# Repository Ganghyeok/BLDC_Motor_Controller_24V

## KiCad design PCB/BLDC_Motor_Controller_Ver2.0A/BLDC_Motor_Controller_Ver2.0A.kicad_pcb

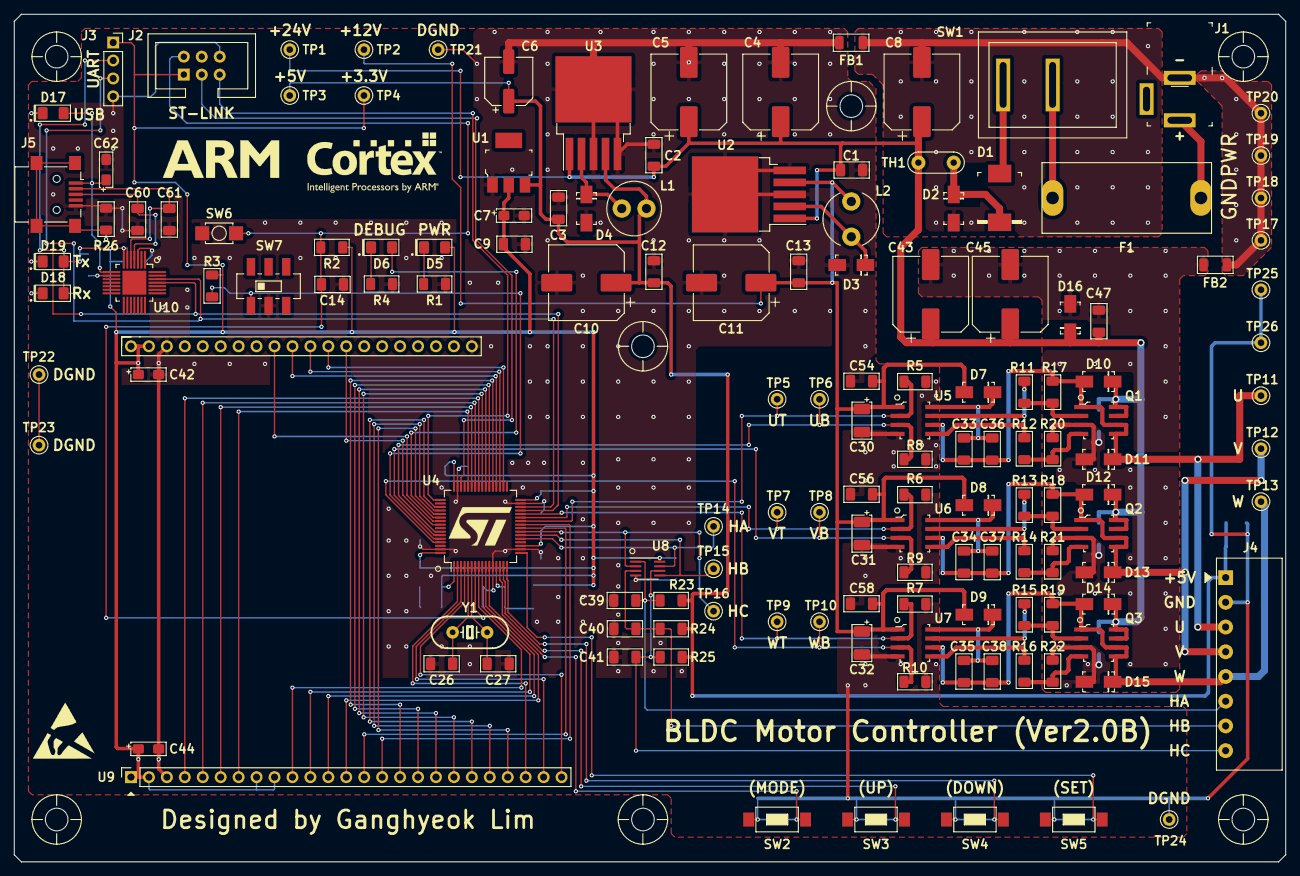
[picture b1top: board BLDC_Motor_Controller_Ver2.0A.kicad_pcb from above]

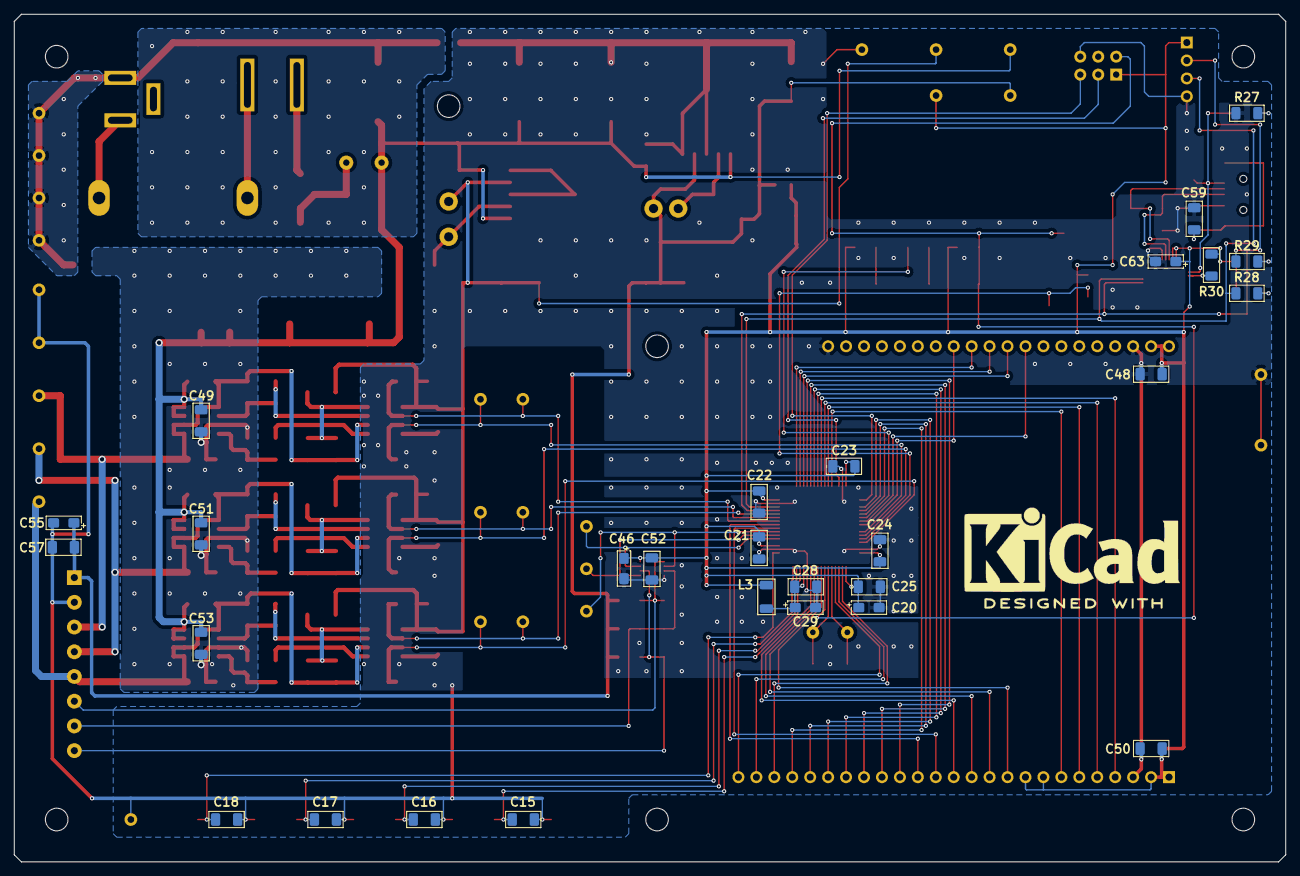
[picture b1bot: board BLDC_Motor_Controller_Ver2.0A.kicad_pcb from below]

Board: 2 copper layers, 180.0 x 120.0 mm, 170 parts (28 on the bottom side), 92 nets.

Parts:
C1, C2, C3, C9, C12, C13, C14, C21, C22, C23, C24, C25, C28, C36, C37, C38, C47, C48, C49, C50, C51, C52, C53, C54, C56, C57, C58, C59: 100nF; C3216_Metric
C4, C5, C8, C10, C11: 330uF/35V; CP_Elec_10x10.5
C6: 100uF/16V; CP_Elec_6.3x5.3
C7, C20, C42, C44, C46, C55: 10uF/16V; C3216_Tantal_Metric
C15, C16, C17, C18: 220nF(ED); C3216_Metric
C26, C27: 20pF; C3216_Metric
C29, C62, C63: 1uF/16V; C3216_Tantal_Metric
C30, C31, C32: 10uF/25V; C3528_Tantal_Metric
C33, C34, C35: 2.2uF; C3216_Metric
C39, C40, C41: 330pF; C3216_Metric
C43, C45: 470uF/35V; CP_Elec_10x10.5
C60, C61: 15pF; C3216_Metric
D1: SS34; DO-214AB
D2, D16: SMAJ24A; DO-214AC
D3, D4: SS13; DO-214AC
D5: LED(POWER); LED_3216_Metric
D6: LED(DEBUG); LED_3216_Metric
D7, D8, D9: SS14; DO-214AC
D10, D11, D12, D13, D14, D15: RS1G; DO-214AC
D17, D18, D19: LED; LED_3216_Metric
F1: 250V/1A; GF-205B(20mm)
FB1, FB2: ED; L3216_Metric
J1: POWER_CONNECTOR; Barrel_Jack_5.5mmODx2.1mmID_PJ-202A
J2: ST-Link_Connector; BHS-01-6P
J3: UART_Connector; PinSocket_1x04_P2.54mm_Vertical
J4: Conn_01x08; Terminal_Block_3.5mm_8P
J5: USB_B_Mini; USB_Mini-B_Lumberg_2486_01_Horizontal
L1: 470uH; L_Radial_D7.5mm_P3.50mm_Fastron_07P
L2: 1mH; L_Radial_D7.8mm_P5.00mm_Fastron_07HCP
L3: 10uH; L3216_Metric
Q1, Q2, Q3: IRF7351PBF; SOIC-8_W3.9mm
R1, R4, R28, R29: 220; R3216_Metric
R2: 100k; R3216_Metric
R3, R5, R6, R7, R8, R9, R10, R17, R18, R19, R20, R21, R22: 10k; R3216_Metric
R11, R12, R13, R14, R15, R16: 22; R3216_Metric
R23, R24, R25, R30: 4.7k; R3216_Metric
R26: 1M; R3216_Metric
R27: 330; R3216_Metric
SW1: SW(POWER); KCD1-101A
SW2: SW(MODE); ITS-1107(SMD)
SW3: SW(UP); ITS-1107(SMD)
SW4: SW(DOWN); ITS-1107(SMD)
SW5: SW(START/STOP); ITS-1107(SMD)
SW6: SW(RESET); SW_TACT_SMD_W3.9mm_L2.9mm_H2mm_GH
SW7: SW(BOOT0); SW_Slide_6P_SMD_GH
TH1: 5D9; NTC-5D-7_9
TP1: TP(+24V); Test_Point(Loop)
TP2: TP(+12V); Test_Point(Loop)
TP3: TP(+5V); Test_Point(Loop)
TP4: TP(+3.3V); Test_Point(Loop)
TP5: UT; Test_Point(Loop)
TP6: UB; Test_Point(Loop)
TP7: VT; Test_Point(Loop)
TP8: VB; Test_Point(Loop)
TP9: WT; Test_Point(Loop)
TP10: WB; Test_Point(Loop)
TP11: U; Test_Point(Loop)
TP12: V; Test_Point(Loop)
TP13: W; Test_Point(Loop)
TP14: HA; Test_Point(Loop)
TP15: HB; Test_Point(Loop)
TP16: HC; Test_Point(Loop)
TP17, TP18, TP19, TP20: AGND; Test_Point(Loop)
TP21, TP22, TP23, TP24, TP25, TP26: DGND; Test_Point(Loop)
U1: LM1117-3.3; SOT-223
U2: LM2575-12BU; TO-263-5_TabPin3
U3: LM2575-5.0BU; TO-263-5_TabPin3
U4: STM32F103RCTx; LQFP-64_10x10mm_P0.5mm
U5, U6, U7: IR2101; SOIC-8_W3.9mm
U8: SN74LVC3G17; SSOP-8_2.95x2.8mm_P0.65mm
U9: TFT-32A
U10: CP2102; VFQFN-28-1EP_5x5mm_HandSolder
Y1: 8MHz; CRYSTAL_HC49_PTH

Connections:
+3.3V: C7.1, C9.1, C20.1, C21.1, C22.1, C23.1, C24.1, C25.1, C42.1, C44.1, C46.1, C48.1, C50.1, C52.1, C63.1, D5.2, D18.2, D19.2, J2.1, J3.1, L3.2, R2.1, R3.1, R30.1, TP4.1, U1.2, U4.1, U4.19, U4.32, U4.48, U4.64, U8.8, U9.1, U9.2, U9.8, U9.9, U9.26, U9.27, U10.6, U10.7
+5V: C3.1, C6.1, C10.1, C12.1, C55.1, C57.1, J4.1, L1.2, R23.1, R24.1, R25.1, TP3.1, U1.3, U3.4
+12V: C11.1, C13.1, C30.1, C31.1, C32.1, C54.1, C56.1, C58.1, D7.A, D8.A, D9.A, L2.2, TP2.1, U2.4, U5.1, U6.1, U7.1
+24V: C1.1, C2.1, C4.1, C5.1, C8.1, C43.1, C45.1, C47.1, C49.1, C51.1, C53.1, D10.K, D12.K, D14.K, D16.K, Q1.7, Q1.8, Q2.7, Q2.8, Q3.7, Q3.8, TH1.1, TP1.1, U2.1, U3.1
BOOT0: R3.2, SW7.1, U4.60
D+: C60.1, J5.3, U10.4
D-: C61.1, J5.2, U10.5
DEBUG1: D6.2, U4.54
GND: C1.2, C2.2, C3.2, C4.2, C5.2, C6.2, C7.2, C9.2, C10.2, C11.2, C12.2, C13.2, C14.2, C15.2, C16.2, C17.2, C18.2, C20.2, C21.2, C22.2, C23.2, C24.2, C25.2, C26.2, C27.2, C28.2, C29.2, C30.2, C31.2, C32.2, C39.2, C40.2, C41.2, C42.2, C44.2, C46.2, C48.2, C50.2, C52.2, C54.2, C55.2, C56.2, C57.2, C58.2, C59.2, C60.2, C61.2, C62.2, C63.2, D3.A, D4.A, FB1.2, J2.6, J3.4, J4.2, J5.5, R1.2, R4.2, R5.2, R6.2, R7.2, R8.2, R9.2, R10.2, R26.1, R27.1, SW2.1, SW3.1, SW4.1, SW5.1, SW6.2, SW7.2, TP21.1, TP22.1, TP23.1, TP24.1, TP25.1, TP26.1, U1.1, U2.3, U2.5, U3.3, U3.5, U4.12, U4.18, U4.31, U4.47, U4.63, U5.4, U6.4, U7.4, U8.4, U9.3, U9.28, U9.45, U10.3
GNDA: C43.2, C45.2, C47.2, C49.2, C51.2, C53.2, D11.A, D13.A, D15.A, D16.A, FB2.1, Q1.3, Q2.3, Q3.3, R20.1, R21.1, R22.1
GNDPWR: C8.2, D2.A, FB1.1, FB2.2, J1.2, TP17.1, TP18.1, TP19.1, TP20.1
HA: TP14.1, U4.21, U8.7
HB: TP15.1, U4.22, U8.5
HC: TP16.1, U4.23, U8.2
NRST: C14.1, J2.2, R2.2, SW6.1, U4.7
unnamed: C26.1, U4.5, Y1.1
unnamed: C27.1, U4.6, Y1.2
unnamed: C28.1, C29.1, L3.1, U4.13
unnamed: C33.1, C36.1, D7.K, U5.8
unnamed: C33.2, C36.2, D10.A, D11.K, J4.3, Q1.1, Q1.5, Q1.6, R17.1, TP11.1, U5.6
unnamed: C34.1, C37.1, D8.K, U6.8
unnamed: C34.2, C37.2, D12.A, D13.K, J4.4, Q2.1, Q2.5, Q2.6, R18.1, TP12.1, U6.6
unnamed: C35.1, C38.1, D9.K, U7.8
unnamed: C35.2, C38.2, D14.A, D15.K, J4.5, Q3.1, Q3.5, Q3.6, R19.1, TP13.1, U7.6
unnamed: C39.1, J4.6, R23.2, U8.1
unnamed: C40.1, J4.7, R24.2, U8.3
unnamed: C41.1, J4.8, R25.2, U8.6
unnamed: C59.1, J5.6, R26.2
unnamed: D1.A, SW1.2
unnamed: D1.K, D2.K, TH1.2
unnamed: D3.K, L2.1, U2.2
unnamed: D4.K, L1.1, U3.2
unnamed: D5.1, R1.1
unnamed: D6.1, R4.1
unnamed: D17.1, R27.2
unnamed: D18.1, R28.2
unnamed: D19.1, R29.2
unnamed: F1.1, SW1.1
unnamed: F1.2, J1.1
unnamed: Q1.2, R11.1, R17.2
unnamed: Q1.4, R12.1, R20.2
unnamed: Q2.2, R13.1, R18.2
unnamed: Q2.4, R14.1, R21.2
unnamed: Q3.2, R15.1, R19.2
unnamed: Q3.4, R16.1, R22.2
unnamed: R11.2, U5.7
unnamed: R12.2, U5.5
unnamed: R13.2, U6.7
unnamed: R14.2, U6.5
unnamed: R15.2, U7.7
unnamed: R16.2, U7.5
unnamed: R30.2, U10.9
SPI2_MISO: U4.35, U9.36
SPI2_MOSI: U4.36, U9.35
SPI2_SCK: U4.34, U9.37
SW1: C15.1, SW2.2, U4.14
SW2: C16.1, SW3.2, U4.15
SW3: C17.1, SW4.2, U4.16
SW4: C18.1, SW5.2, U4.17
SWCLK: J2.5, U4.49
SWDIO: J2.3, U4.46
TFT_D0: U4.8, U9.10
TFT_D1: U4.9, U9.11
TFT_D2: U4.10, U9.12
TFT_D3: U4.11, U9.13
TFT_D4: U4.24, U9.14
TFT_D5: U4.25, U9.15
TFT_D6: U4.37, U9.16
TFT_D7: U4.38, U9.17
TFT_D8: U4.39, U9.18
TFT_D9: U4.40, U9.19
TFT_D10: U4.51, U9.20
TFT_D11: U4.52, U9.21
TFT_D12: U4.53, U9.22
TFT_D13: U4.2, U9.23
TFT_D14: U4.3, U9.24
TFT_D15: U4.4, U9.25
TFT_RS: U4.43, U9.6
UART3_RX: J3.3, R28.1, U4.30, U10.26
UART3_TX: J3.2, R29.1, U4.29, U10.25
UB: R8.1, TP6.1, U4.58, U5.3
UT: R5.1, TP5.1, U4.26, U5.2
VB: R9.1, TP8.1, U4.59, U6.3
VBUS: C62.1, D17.2, J5.1, U10.8
VT: R6.1, TP7.1, U4.27, U6.2
WB: R10.1, TP10.1, U4.61, U7.3
WT: R7.1, TP9.1, U4.28, U7.2
~TFT_CS: U4.42, U9.5
~TFT_RST: U4.41, U9.4
~TFT_WR: U4.44, U9.7
~TS_CS: U4.55, U9.34
~TS_INT: U4.56, U9.38

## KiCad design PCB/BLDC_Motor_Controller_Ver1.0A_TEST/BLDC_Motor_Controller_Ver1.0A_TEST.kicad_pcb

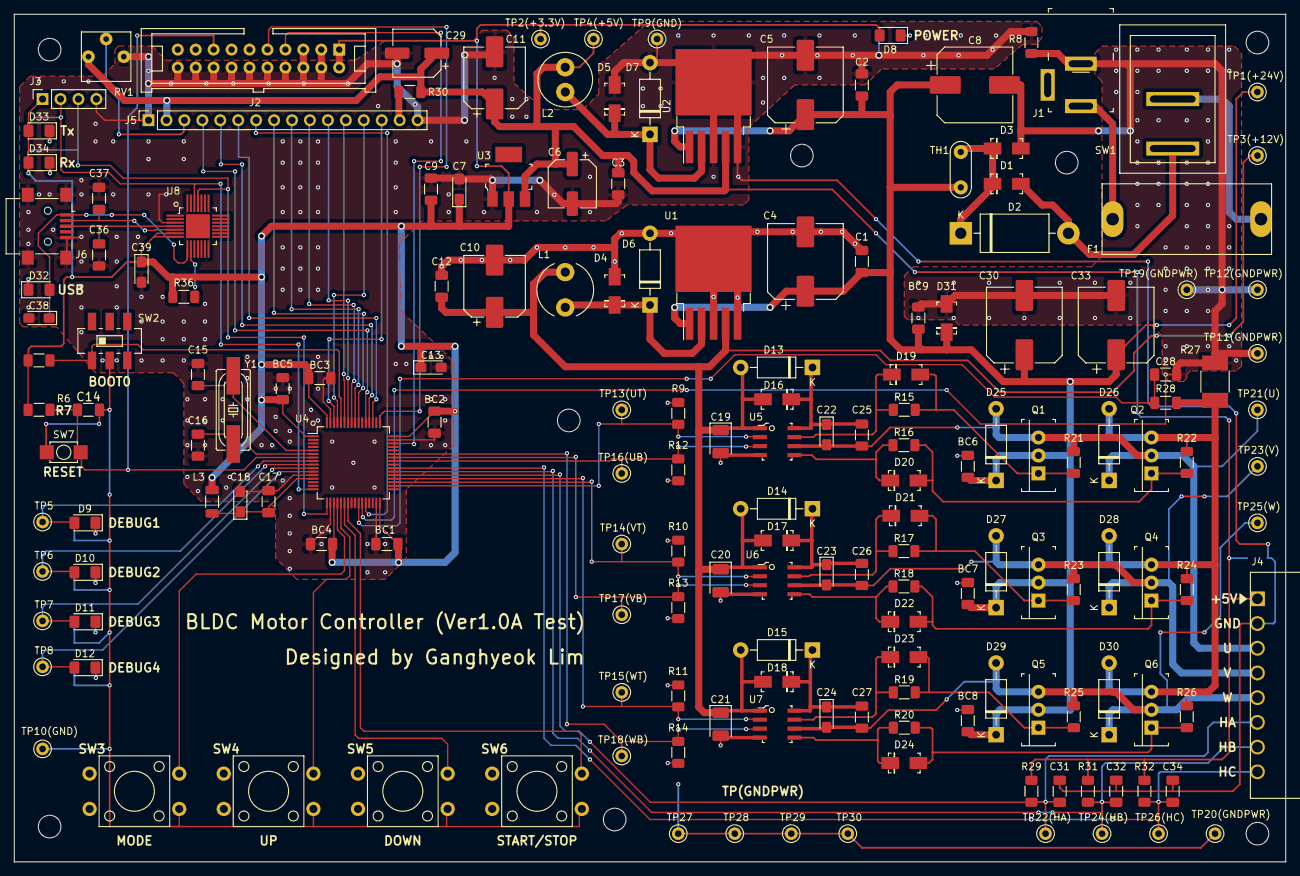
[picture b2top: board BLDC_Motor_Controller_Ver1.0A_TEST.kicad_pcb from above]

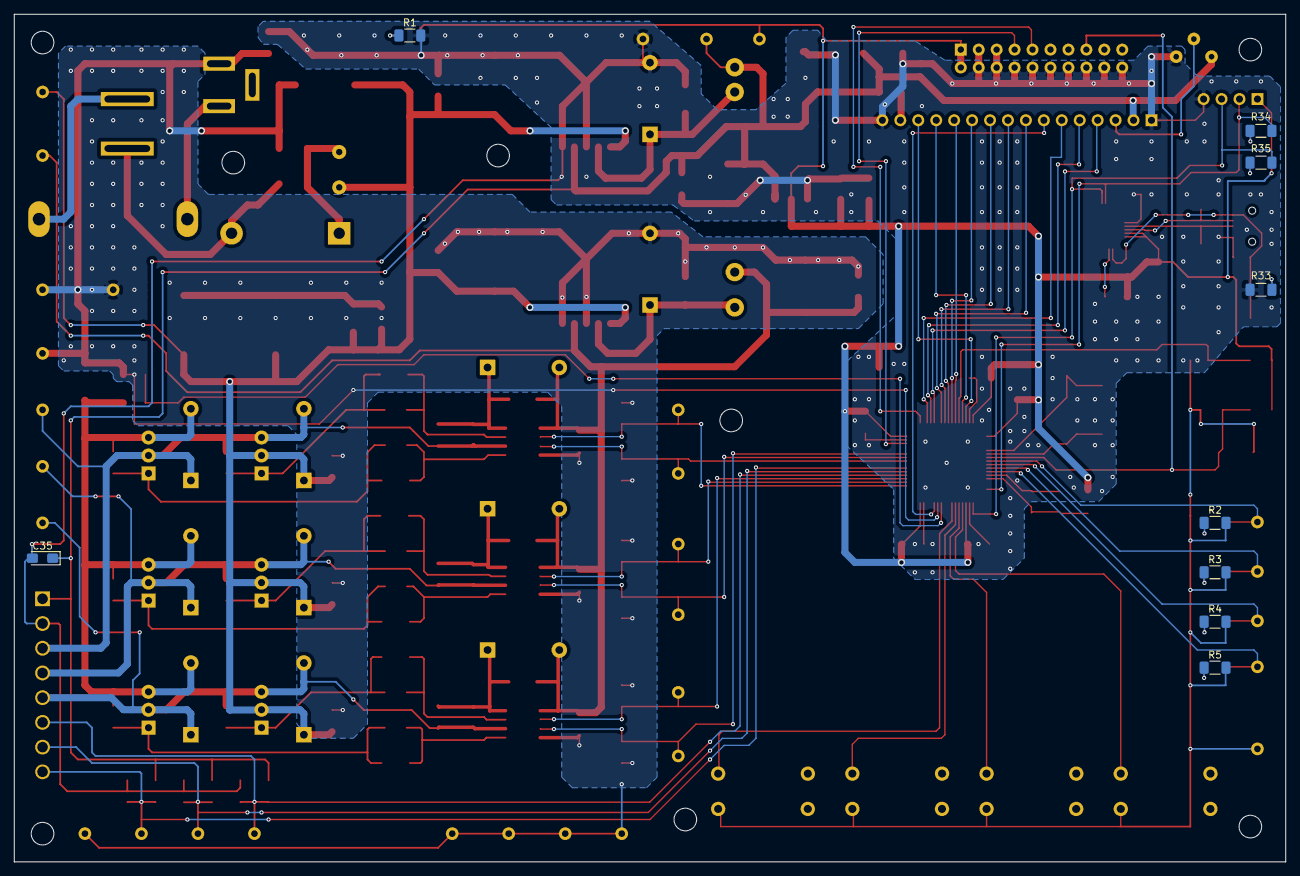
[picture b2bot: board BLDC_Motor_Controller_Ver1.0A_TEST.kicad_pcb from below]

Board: 2 copper layers, 180.0 x 120.0 mm, 182 parts (9 on the bottom side), 83 nets.

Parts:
BC1, BC2, BC3, BC4, BC5, BC6, BC7, BC8, BC9: 100nF; C_1206_3216Metric_Pad1.33x1.80mm_HandSolder
C1, C2, C3, C9, C12, C14, C17, C25, C26, C27: 100nF; C_1206_3216Metric_Pad1.33x1.80mm_HandSolder
C4, C5: 330uF/35V; CP_Elec_10x10.5
C6, C29: 100uF/16V; CP_Elec_6.3x5.3
C7, C35: 10uF/16V; CP_EIA-3216-18_Kemet-A_Pad1.58x1.35mm_HandSolder
C8: 470uF/35V; CP_Elec_10x10.5
C10, C11: 330uF/16V; CP_Elec_8x10.5
C13: 10uF; CP_EIA-3216-18_Kemet-A_Pad1.58x1.35mm_HandSolder
C15, C16: 20pF; C_1206_3216Metric_Pad1.33x1.80mm_HandSolder
C18, C38, C39: 1uF; CP_EIA-3216-18_Kemet-A_Pad1.58x1.35mm_HandSolder
C19, C20, C21: 10uF/25V; CP_EIA-3528-21_Kemet-B_Pad1.50x2.35mm_HandSolder
C22, C23, C24: 2.2uF; CP_EIA-3216-18_Kemet-A_Pad1.58x1.35mm_HandSolder
C28: ED; C_1206_3216Metric_Pad1.33x1.80mm_HandSolder
C30, C33: 470uF; CP_Elec_10x10.5
C31, C32, C34: 330pF; C_1206_3216Metric_Pad1.33x1.80mm_HandSolder
C36, C37: 15pF; C_1206_3216Metric_Pad1.33x1.80mm_HandSolder
D1: SS24; DO-214AC
D2: 1N5822; D_DO-201AD_P15.24mm_Horizontal
D3, D31: SMAJ24A; DO-214AC
D4, D5: SS13(NC); DO-214AC
D6, D7: 1N5818; D_DO-41_SOD81_P10.16mm_Horizontal
D8: LED(POWER); LED_1206_3216Metric_Pad1.42x1.75mm_HandSolder
D9: LED(DEBUG1); LED_1206_3216Metric_Pad1.42x1.75mm_HandSolder
D10: LED(DEBUG2); LED_1206_3216Metric_Pad1.42x1.75mm_HandSolder
D11: LED(DEBUG3); LED_1206_3216Metric_Pad1.42x1.75mm_HandSolder
D12: LED(DEBUG4); LED_1206_3216Metric_Pad1.42x1.75mm_HandSolder
D13, D14, D15: 1N5819(NC); D_DO-41_SOD81_P10.16mm_Horizontal
D16, D17, D18, D19, D20, D21, D22, D23, D24: SS14; DO-214AC
D25, D26, D27, D28, D29, D30: FR104; D_DO-41_SOD81_P10.16mm_Horizontal
D32, D33, D34: LED; LED_1206_3216Metric_Pad1.42x1.75mm_HandSolder
F1: 250V/2A; GF-205B(20mm)
J1: POWER_CONNECTOR; Barrel_Jack_5.5mmODx2.1mmID_PJ-202A
J2: ST-Link_Connector; HIF3F-20PA-2.54DSA_GH
J3: UART_Connector; PinSocket_1x04_P2.54mm_Vertical
J4: Motor_Connector; ECH350R(8P)
J5: LCD_Connector; PinSocket_1x16_P2.54mm_Vertical
J6: USB_B_Mini; USB_Mini-B_Lumberg_2486_01_Horizontal
L1: 1mH; L_Radial_D7.8mm_P5.00mm_Fastron_07HCP
L2: 470uH; L_Radial_D7.5mm_P3.50mm_Fastron_07P
L3: 10uH; L_1206_3216Metric_Pad1.22x1.90mm_HandSolder
Q1, Q2, Q3, Q4, Q5, Q6: IRFZ44N; TO-220-3
R1, R2, R3, R4, R5, R34, R35: 150; R_1206_3216Metric_Pad1.30x1.75mm_HandSolder
R6, R9, R10, R11, R12, R13, R14, R21, R22, R23, R24, R25, R26: 10k; R_1206_3216Metric_Pad1.30x1.75mm_HandSolder
R7: 100k; R_1206_3216Metric_Pad1.30x1.75mm_HandSolder
R8: 0; R_1206_3216Metric_Pad1.30x1.75mm_HandSolder
R15, R16, R17, R18, R19, R20: 22; R_1206_3216Metric_Pad1.30x1.75mm_HandSolder
R27: 0.1/1W; LR2512-21R100F4
R28: ED; R_1206_3216Metric_Pad1.30x1.75mm_HandSolder
R29, R31, R32, R36: 4.7k; R_1206_3216Metric_Pad1.30x1.75mm_HandSolder
R30: 47; R_1206_3216Metric_Pad1.30x1.75mm_HandSolder
R33: 330; R_1206_3216Metric_Pad1.30x1.75mm_HandSolder
RV1: 10k; Tocos_GF063P
SW1: SW(POWER); KCD1-101A
SW2: SW(BOOT0); SW_Slide_6P_SMD_GH
SW3: SW(MODE); ITS-1103W
SW4: SW(UP); ITS-1103W
SW5: SW(DOWN); ITS-1103W
SW6: SW(START/STOP); ITS-1103W
SW7: SW(RESET); SW_TACT_SMD_W3.9mm_L2.9mm_H2mm_GH
TH1: NTC; NTC-5D-7_9
TP1(+24V): TP(+24V); Test_Point(Loop)
TP2(+3.3V): TP(+3.3V); Test_Point(Loop)
TP3(+12V): TP(+12V); Test_Point(Loop)
TP4(+5V): TP(+5V); Test_Point(Loop)
TP5: TP(DEBUG1); Test_Point(Loop)
TP6: TP(DEBUG2); Test_Point(Loop)
TP7: TP(DEBUG3); Test_Point(Loop)
TP8: TP(DEBUG4); Test_Point(Loop)
TP9(GND), TP10(GND): TP(GND); Test_Point(Loop)
TP11(GNDPWR), TP12(GNDPWR), TP19(GNDPWR), TP20(GNDPWR), TP27, TP28, TP29, TP30: TP(GNDPWR); Test_Point(Loop)
TP13(UT): TP(UT); Test_Point(Loop)
TP14(VT): TP(VT); Test_Point(Loop)
TP15(WT): TP(WT); Test_Point(Loop)
TP16(UB): TP(UB); Test_Point(Loop)
TP17(VB): TP(VB); Test_Point(Loop)
TP18(WB): TP(WB); Test_Point(Loop)
TP21(U): TP(U); Test_Point(Loop)
TP22(HA): TP(HA); Test_Point(Loop)
TP23(V): TP(V); Test_Point(Loop)
TP24(HB): TP(HB); Test_Point(Loop)
TP25(W): TP(W); Test_Point(Loop)
TP26(HC): TP(HC); Test_Point(Loop)
U1: LM2575-12BU; TO-263-5_TabPin3
U2: LM2575-5.0BU; TO-263-5_TabPin3
U3: LM1117-3.3; SOT-223
U4: STM32F103RCT6; LQFP-64_10x10mm_P0.5mm
U5, U6, U7: IR2101; SOIC-8_W3.9mm
U8: CP2102; VFQFN-28-1EP_5x5mm_HandSolder
Y1: 8MHz; CRYSTAL_HC49_SMD

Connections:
+3.3V: BC1.1, BC2.1, BC3.1, BC4.1, BC5.1, C7.1, C9.1, C13.1, C39.1, D8.2, D33.2, D34.2, J2.1, J2.2, J3.1, L3.2, R6.1, R7.1, R36.2, TP2(+3.3V).1, U3.2, U4.1, U4.19, U4.32, U4.48, U4.64, U8.6, U8.7
+5V: C3.1, C6.1, C11.1, C29.1, C35.1, J4.1, J5.2, L2.2, R29.1, R30.2, R31.1, R32.1, RV1.1, TP4(+5V).1, U2.4, U3.3
+12V: C10.1, C12.1, C19.1, C20.1, C21.1, D13.2, D14.2, D15.2, D16.A, D17.A, D18.A, L1.2, TP3(+12V).1, U1.4, U5.1, U6.1, U7.1
+24V: BC6.1, BC7.1, BC8.1, BC9.1, C1.1, C2.1, C4.1, C5.1, C8.1, C30.1, C33.1, D25.1, D27.1, D29.1, D31.K, Q1.2, Q3.2, Q5.2, TH1.1, TP1(+24V).1, U1.1, U2.1
/sheet5FA8433B/A: J5.15, R30.1
/sheet5FA8433B/V0: J5.3, RV1.2
BOOT0: R6.2, SW2.1, U4.60
CURRENT: C28.1, R28.2, U4.26
D+: C36.1, J6.3, U8.4
D-: C37.1, J6.2, U8.5
DEBUG1: D9.2, TP5.1, U4.8
DEBUG2: D10.2, TP6.1, U4.9
DEBUG3: D11.2, TP7.1, U4.10
DEBUG4: D12.2, TP8.1, U4.11
GND: BC1.2, BC2.2, BC3.2, BC4.2, BC5.2, C2.2, C3.2, C5.2, C6.2, C7.2, C9.2, C11.2, C13.2, C14.2, C15.2, C16.2, C17.2, C18.2, C29.2, C31.2, C32.2, C34.2, C35.2, C36.2, C37.2, C38.2, C39.2, D5.A, D7.2, J2.3, J2.4, J2.5, J2.6, J2.8, J2.10, J2.12, J2.14, J2.16, J2.18, J2.20, J3.4, J4.2, J5.1, J5.16, J6.5, J6.6, R1.2, R2.2, R3.2, R4.2, R5.2, R8.2, R33.2, RV1.3, SW2.2, SW3.1, SW4.1, SW5.1, SW6.1, SW7.2, TP9(GND).1, TP10(GND).1, U2.3, U2.5, U3.1, U4.12, U4.18, U4.31, U4.47, U4.63, U8.3
GNDPWR: BC6.2, BC7.2, BC8.2, BC9.2, C1.2, C4.2, C8.2, C10.2, C12.2, C19.2, C20.2, C21.2, C28.2, C30.2, C33.2, D3.A, D4.A, D6.2, D31.A, J1.2, R8.1, R9.1, R10.1, R11.1, R12.1, R13.1, R14.1, R27.2, TP11(GNDPWR).1, TP12(GNDPWR).1, TP19(GNDPWR).1, TP20(GNDPWR).1, TP27.1, TP28.1, TP29.1, TP30.1, U1.3, U1.5, U4.27, U5.4, U6.4, U7.4
HA: C31.1, J4.6, R29.2, TP22(HA).1, U4.37
HB: C32.1, J4.7, R31.2, TP24(HB).1, U4.38
HC: C34.1, J4.8, R32.2, TP26(HC).1, U4.39
LCD_D0: J5.7, U4.28
LCD_D1: J5.8, U4.55
LCD_D2: J5.9, U4.56
LCD_D3: J5.10, U4.57
LCD_D4: J5.11, U4.58
LCD_D5: J5.12, U4.59
LCD_D6: J5.13, U4.61
LCD_D7: J5.14, U4.62
LCD_E: J5.6, U4.51
LCD_RS: J5.4, U4.53
LCD_RW: J5.5, U4.52
NRST: C14.1, J2.15, R7.2, SW7.1, U4.7
unnamed: C15.1, U4.5, Y1.1
unnamed: C16.1, U4.6, Y1.2
unnamed: C17.1, C18.1, L3.1, U4.13
unnamed: C22.1, C25.1, D13.1, D16.K, U5.8
unnamed: C22.2, C25.2, D25.2, D26.1, J4.3, Q1.3, Q2.2, R21.2, TP21(U).1, U5.6
unnamed: C23.1, C26.1, D14.1, D17.K, U6.8
unnamed: C23.2, C26.2, D27.2, D28.1, J4.4, Q3.3, Q4.2, R23.2, TP23(V).1, U6.6
unnamed: C24.1, C27.1, D15.1, D18.K, U7.8
unnamed: C24.2, C27.2, D29.2, D30.1, J4.5, Q5.3, Q6.2, R25.2, TP25(W).1, U7.6
unnamed: D1.A, D2.2, SW1.2
unnamed: D1.K, D2.1, D3.K, TH1.2
unnamed: D4.K, D6.1, L1.1, U1.2
unnamed: D5.K, D7.1, L2.1, U2.2
unnamed: D8.1, R1.1
unnamed: D9.1, R2.1
unnamed: D10.1, R3.1
unnamed: D11.1, R4.1
unnamed: D12.1, R5.1
unnamed: D19.A, Q1.1, R15.2, R21.1
unnamed: D19.K, R15.1, U5.7
unnamed: D20.A, Q2.1, R16.2, R22.1
unnamed: D20.K, R16.1, U5.5
unnamed: D21.A, Q3.1, R17.2, R23.1
unnamed: D21.K, R17.1, U6.7
unnamed: D22.A, Q4.1, R18.2, R24.1
unnamed: D22.K, R18.1, U6.5
unnamed: D23.A, Q5.1, R19.2, R25.1
unnamed: D23.K, R19.1, U7.7
unnamed: D24.A, Q6.1, R20.2, R26.1
unnamed: D24.K, R20.1, U7.5
unnamed: D26.2, D28.2, D30.2, Q2.3, Q4.3, Q6.3, R22.2, R24.2, R26.2, R27.1, R28.1
unnamed: D32.1, R33.1
unnamed: D33.1, R34.2
unnamed: D34.1, R35.2
unnamed: F1.1, SW1.1
unnamed: F1.2, J1.1
unnamed: R36.1, U8.9
RXD: J3.3, R35.1, U4.17, U8.25
SW1: SW3.2, U4.20
SW2: SW4.2, U4.21
SW3: SW5.2, U4.22
SW4: SW6.2, U4.23
SWCLK: J2.9, U4.49
SWDIO: J2.7, U4.46
TXD: J3.2, R34.1, U4.16, U8.26
UB: R12.2, TP16(UB).1, U4.41, U5.3
UT: R9.2, TP13(UT).1, U4.34, U5.2
VB: R13.2, TP17(VB).1, U4.42, U6.3
VBUS: C38.1, D32.2, J6.1, U8.8
VT: R10.2, TP14(VT).1, U4.35, U6.2
WB: R14.2, TP18(WB).1, U4.43, U7.3
WT: R11.2, TP15(WT).1, U4.36, U7.2

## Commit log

2020-12-18 [Add] Schematic, PCB files, Firmware
2020-12-18 [Test] UART_Transmit_IT
    -Test (PASS) UART_Transmit_IT
2020-12-19 [Test] TIM Base interrupt generation
    -Test (PASS) TIM Base interrupt generation
2020-12-19 [Test] TIM PWM generation for ch1~4
    - Test (PASS) TIM PWM generation for ch1~4 with arbitrary duty
2020-12-19 [Add & Test] Remapping of TIM3 port
    - Add AFIO Remapping Macro of TIM3
    - Test Remapping port of TIM3 and PWM generation test for ch1~4 with Remapped port(PC6/7/8/9)
2021-01-01 [Add] BLDC drive with Hall sensor
2021-01-02 [Refactor] Refactor the code
2021-01-03 [Add & Refactor & Fix] See the details
    - Add Start or Stop BLDC motor by using Button
    - Fix 'BLDC_BootstrapCap_Charge' function
    - Refactoring Refactor the entire code for Readability and Extensibility
    Introduce BLDC Handler that makes the manipulation of BLDC functions
2021-01-05 [Add] Function to Get Rotor Position(deg)
    - Add Function to Get Rotor Position(deg)
    UART2 to transmit data to PC
2021-01-05 [Add] Add function to Get Rotor Speed(rpm)
    - Add Add function to Get Rotor Speed(rpm)
    - Fix Change the period of TIM6 interrupt
2021-01-07 [Add] Add UART2 Transmission with DMA(Hardcoded)
    - Add Transmit Motor speed value to PC by using UART2 DMA mode
2021-01-09 [Add] UART2 Transmission with DMA (Extensible)
    - Add Transmit Motor speed value(CW/CCW) to PC by using UART2 DMA mode (with DMA driver)
2021-01-10 [Add] PID Speed Control
    - Add PID Speed Control Code & Test figures with various Kp, Ki, Kd
2021-01-11 [Add] PID Position Control
    - Add PID Position Control Code
2021-01-12 [Fix] PID Position Control
    - Fix Change TIM_PSC, TIM_ARR value of TIM4 which generates PWM signal, in order to adjust the PWM duty cycle precisely.
    Remove the mimimum PWM duty cycle value '5', I think it is useless
2021-01-13 [Add] PID Position Control with Speed profile
    - Add PID Position Control with Trapezoidal & Isosceles triangle Speed profile.
    -> It works well, but it still needs precise adjustment (ex. "Vibration depends on Acceleration, Kp, Ki" / "Trajectory generation function", etc.)
    -> it also needs some Refactoring
2021-01-17 [Add] TFT LCD Control & Touch Screen data aqsitn
    - Add TFT LCD Control APIs
    Touch Screen data aquisition APIs
2021-01-18 [Update] Touch Screen data aquisition API
2021-01-18 [Fix] TFT LCD pin change
    - Fix TFT LCD pin change
    TFT_nRST : PA0 -> PA8
    TFT_nCS : PA1 -> PA9
    TFT_RS : PA2 -> PA10
    TFT_nWR : PA3 -> PA11
2021-01-19 [Fix] Pin change for Hall sensor & UART
    - Fix HA : PC6 -> PA5
    HB : PC7 -> PA6
    HC : PC8 -> PA7
    UART2_TX(PA2) -> UART3_TX(PB10)
    UART2_RX(PA3) -> UART3_RX(PB11)
    SW(Emergency Stop) : PA7 -> PA4
2021-01-19 [Refactor & Test] PID position tracking with TFT
    - Test PID position tracking with displaying touch screen input
2021-01-20 [Refactor & Test] PID speed with TFT
    - Test PID speed with displaying touch screen input
2021-01-20 [Add] 5 of Keys with Debouncing Caps(220nF)
    - Add Key1 : MODE
    Key2 : UP
    Key3 : DOWN
    Key4 : START/STOP
    Key5 : EMERGENCY STOP
2021-01-23 [Add] Graph of Speed / Position value
2021-02-27 [Add] PCB design & Firmware funcitons
